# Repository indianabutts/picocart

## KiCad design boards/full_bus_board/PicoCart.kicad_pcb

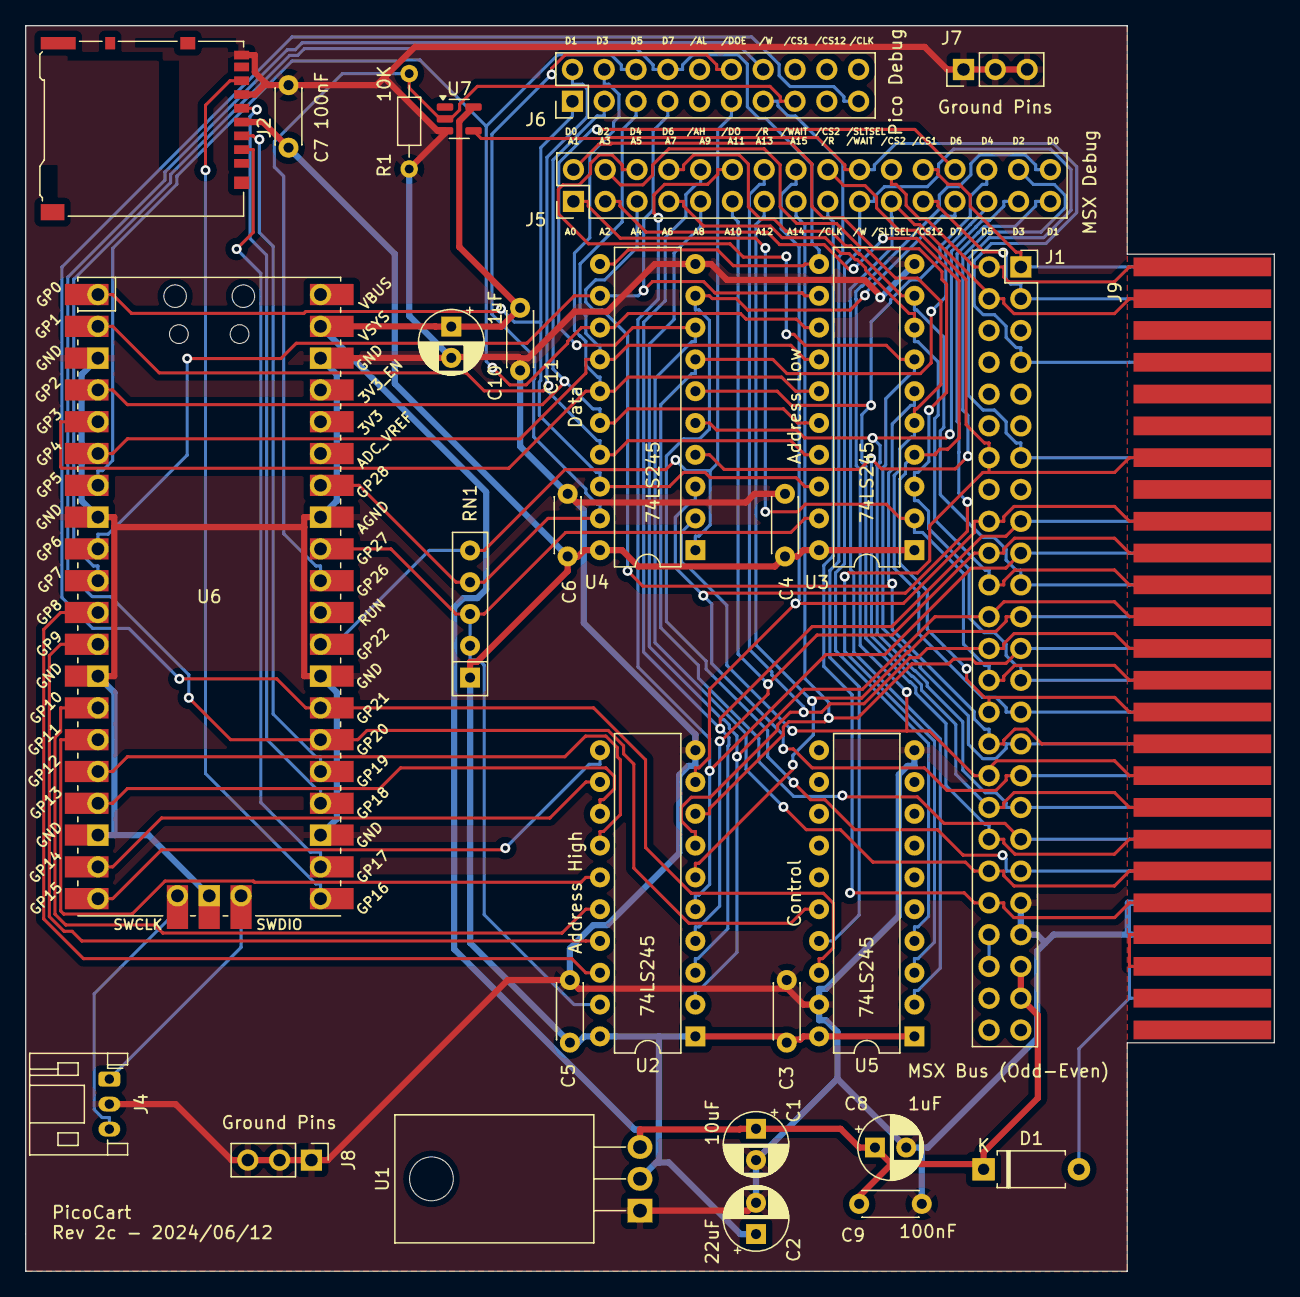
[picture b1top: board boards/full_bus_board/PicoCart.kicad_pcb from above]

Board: 2 copper layers, 99.8 x 99.5 mm, 29 parts (0 on the bottom side), 67 nets.

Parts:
C1: 10uF; CP_Radial_D5.0mm_P2.50mm
C2: 22uF; CP_Radial_D5.0mm_P2.50mm
C3, C4, C5, C6, C7, C9, C11: 100nF; C_Disc_D4.3mm_W1.9mm_P5.00mm
C8, C10: 1uF; CP_Radial_D5.0mm_P2.50mm
D1: D; D_A-405_P7.62mm_Horizontal
J1: MSX Bus (Odd-Even); PinHeader_2x25_P2.54mm_Vertical
J2: Micro_SD_Card; microSD_HC_Hirose_DM3AT-SF-PEJM5
J4: DEBUG; JST_PH_S3B-PH-K_1x03_P2.00mm_Horizontal
J5: MSX Debug; PinHeader_2x16_P2.54mm_Vertical
J6: Pico Debug; PinHeader_2x10_P2.54mm_Vertical
J7, J8: Ground Pins; PinHeader_1x03_P2.54mm_Vertical
J9: Edge Connector; MSX_Cartridge
R1: 10K; R_Axial_DIN0204_L3.6mm_D1.6mm_P7.62mm_Horizontal
RN1: 10K; R_Array_SIP5
U1: LD1117S33TR_SOT223; TO-220-3_Horizontal_TabDown
U2, U3, U4, U5: 74LS245; DIP-20_W7.62mm
U6: Pico; RPi_Pico_SMD_TH
U7: SN74LV1T34DBV; SOT-23-5

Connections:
+3.3V: C2.1, C3.1, C4.1, C5.1, C6.1, C7.1, J2.4 (VDD), RN1.1 (R1.1), U1.2 (VO), U2.1 (A->B), U2.20 (VCC), U3.1 (A->B), U3.20 (VCC), U4.20 (VCC), U5.1 (A->B), U5.20 (VCC)
+5V: C1.1, C8.1, C9.1, C10.1, C11.1, D1.1 (K), J1.45, J1.47, U1.3 (VI), U6.39 (VSYS), U7.5 (VCC)
/E_A0: J1.28, J5.1, J9.28, U3.2 (A0)
/E_A1: J1.27, J5.2, J9.27, U3.3 (A1)
/E_A2: J1.30, J5.3, J9.30, U3.4 (A2)
/E_A3: J1.29, J5.4, J9.29, U3.5 (A3)
/E_A4: J1.32, J5.5, J9.32, U3.6 (A4)
/E_A5: J1.31, J5.6, J9.31, U3.7 (A5)
/E_A6: J1.22, J5.7, J9.22, U3.8 (A6)
/E_A7: J1.21, J5.8, J9.21, U3.9 (A7)
/E_A8: J1.24, J5.9, J9.24, U2.2 (A0)
/E_A9: J1.17, J5.10, J9.17, U2.3 (A1)
/E_A10: J1.20, J5.11, J9.20, U2.4 (A2)
/E_A11: J1.19, J5.12, J9.19, U2.5 (A3)
/E_A12: J1.23, J5.13, J9.23, U2.6 (A4)
/E_A13: J1.26, J5.14, J9.26, U2.7 (A5)
/E_A14: J1.25, J5.15, J9.25, U2.8 (A6)
/E_A15: J1.18, J5.16, J9.18, U2.9 (A7)
/E_D0: J1.34, J5.32, J9.34, U4.2 (A0)
/E_D1: J1.33, J5.31, J9.33, U4.3 (A1)
/E_D2: J1.36, J5.30, J9.36, U4.4 (A2)
/E_D3: J1.35, J5.29, J9.35, U4.5 (A3)
/E_D4: J1.38, J5.28, J9.38, U4.6 (A4)
/E_D5: J1.37, J5.27, J9.37, U4.7 (A5)
/E_D6: J1.40, J5.26, J9.40, U4.8 (A6)
/E_D7: J1.39, J5.25, J9.39, U4.9 (A7)
/I_D0: J6.1, U3.18 (B0), U4.18 (B0), U6.1 (GPIO0)
/I_D1: J6.2, U3.17 (B1), U4.17 (B1), U6.2 (GPIO1)
/I_D2: J6.3, U3.16 (B2), U4.16 (B2), U6.4 (GPIO2)
/I_D3: J6.4, U3.15 (B3), U4.15 (B3), U6.5 (GPIO3)
/I_D4: J6.5, U3.14 (B4), U4.14 (B4), U6.6 (GPIO4)
/I_D5: J6.6, U3.13 (B5), U4.13 (B5), U6.7 (GPIO5)
/I_D6: J6.7, U3.12 (B6), U4.12 (B6), U6.9 (GPIO6)
/I_D7: J6.8, U3.11 (B7), U4.11 (B7), U6.10 (GPIO7)
/I_D8: U2.18 (B0), U6.11 (GPIO8)
/I_D9: U2.17 (B1), U6.12 (GPIO9)
/I_D10: U2.16 (B2), U6.14 (GPIO10)
/I_D11: U2.15 (B3), U6.15 (GPIO11)
/I_D12: U2.14 (B4), U6.16 (GPIO12)
/I_D13: U2.13 (B5), U6.17 (GPIO13)
/I_D14: U2.12 (B6), U6.19 (GPIO14)
/I_D15: U2.11 (B7), U6.20 (GPIO15)
E_CLK: J1.42, J5.17, J9.42
GND: C1.2, C2.2, C3.2, C4.2, C5.2, C6.2, C7.2, C8.2, C9.2, C10.2, C11.2, J1.41, J1.43, J2.6 (VSS), J2.9 (SHIELD), J4.2, J7.1, J7.2, J7.3, J8.1, J8.2, J8.3, J9.41, J9.43, R1.1, U1.1 (GND), U2.10 (GND), U3.10 (GND), U4.10 (GND), U5.10 (GND), U5.19 (CE), U6.3 (GND), U6.8 (GND), U6.13 (GND), U6.18 (GND), U6.23 (GND), U6.28 (GND), U6.33 (AGND), U6.38 (GND), U6.42 (GND), U7.3 (GND)
unnamed: D1.2 (A), J9.45, J9.47
unnamed: J1.44, J1.46
unnamed: J4.1, U6.43 (SWDIO)
unnamed: J4.3, U6.41 (SWCLK)
unnamed: J9.44, J9.46
SPI_CS: J2.2 (DAT3/CD), U6.22 (GPIO17)
SPI_MISO: J2.7 (DAT0), U6.21 (GPIO16)
SPI_MOSI: J2.3 (CMD), U6.25 (GPIO19)
SPI_SCK: J2.5 (CLK), U6.24 (GPIO18)
/AOE: RN1.2 (R1.2), RN1.3 (R2.2), U2.19 (CE), U3.19 (CE), U6.32 (GPIO27_ADC1)
/DOE: J6.12, RN1.4 (R3.2), U4.19 (CE), U6.34 (GPIO28_ADC2)
/DOUT: J6.11, RN1.5 (R4.2), U4.1 (A->B), U6.29 (GPIO22)
/E_CS1: J1.1, J5.24, J9.1
/E_CS2: J1.2, J5.22, J9.2
/E_CS12: J1.3, J5.23, J9.3
/E_READ: J1.14, J5.18, J9.14, U5.3 (A1)
/E_SLTSEL: J1.4, J5.21, J9.4, U5.2 (A0)
/E_WRITE: J1.13, J5.19, J9.13, U5.4 (A2)
/I_READ: J6.13, U5.17 (B1)
/I_SLTSEL: J6.19, U5.18 (B0), U6.27 (GPIO21)
/I_WAIT: J6.15, R1.2, U6.31 (GPIO26_ADC0), U7.2 (A)
/I_WRITE: J6.14, U5.16 (B2), U6.26 (GPIO20)
/WAIT: J1.7, J5.20, J9.7, U7.4 (Y)

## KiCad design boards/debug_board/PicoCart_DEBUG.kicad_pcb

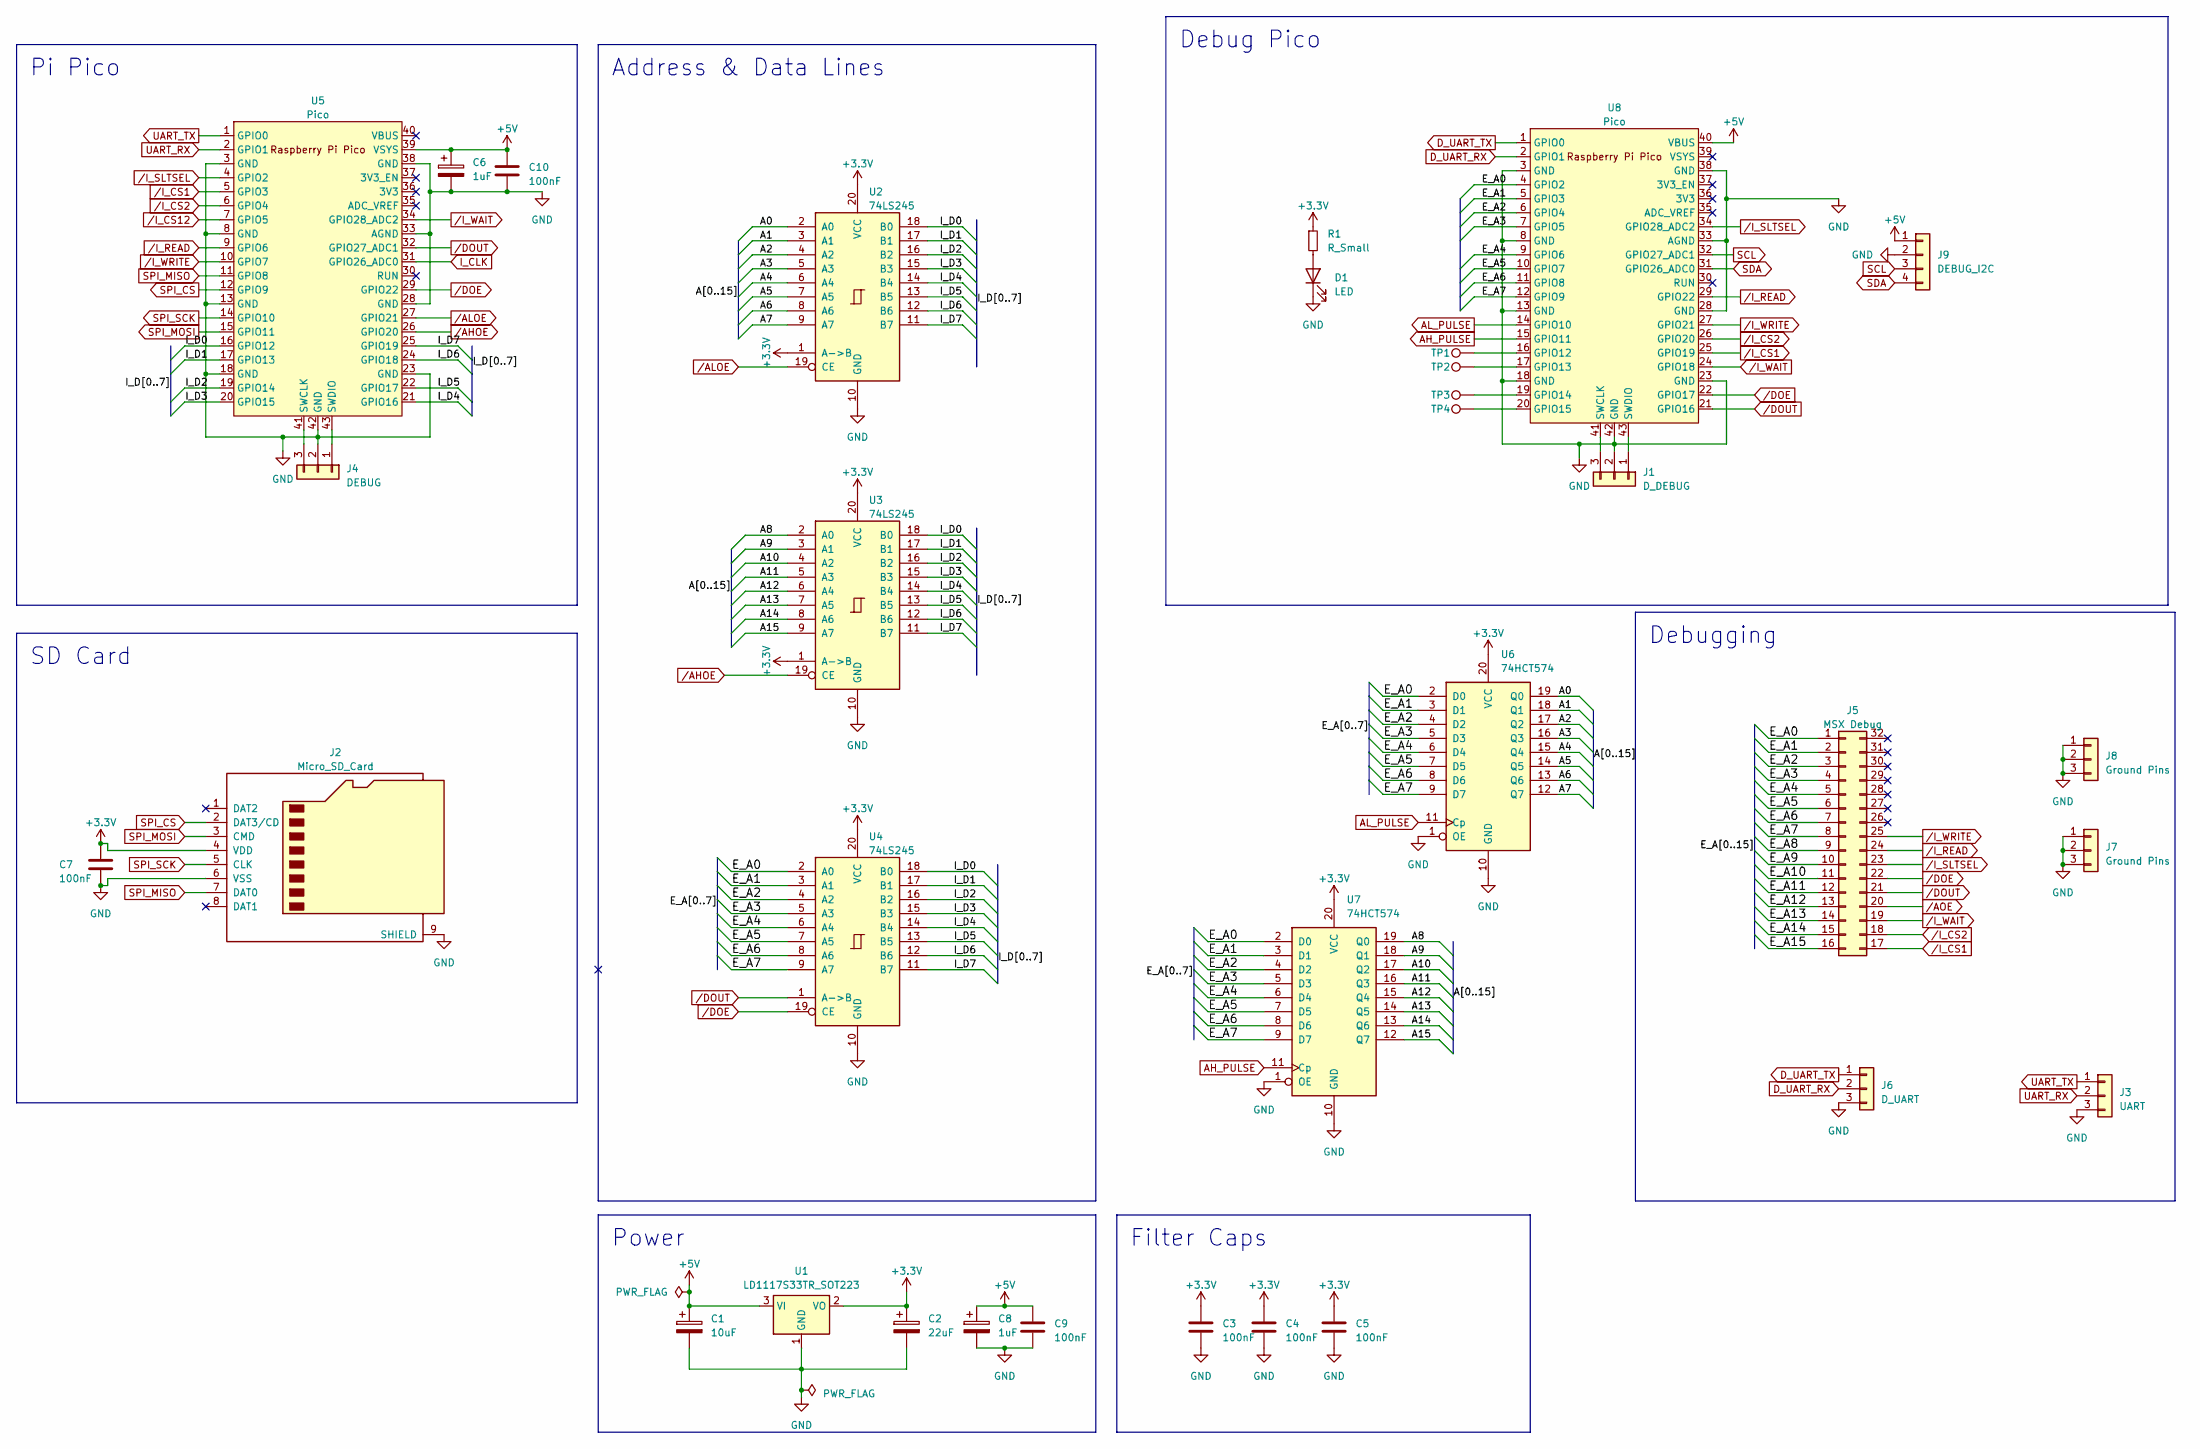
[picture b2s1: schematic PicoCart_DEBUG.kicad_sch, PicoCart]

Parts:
C1: 10uF; CP_Radial_D5.0mm_P2.50mm
C2: 22uF; CP_Radial_D5.0mm_P2.50mm
C3, C4, C5, C7, C9, C10: 100nF; C_Disc_D4.3mm_W1.9mm_P5.00mm
C6, C8: 1uF; CP_Radial_D5.0mm_P2.50mm
D1: LED; LED_D5.0mm
J1: D_DEBUG; PinSocket_1x03_P2.54mm_Vertical
J2: Micro_SD_Card; microSD_HC_Hirose_DM3AT-SF-PEJM5
J3: UART; PinSocket_1x03_P2.54mm_Vertical
J4: DEBUG; PinSocket_1x03_P2.54mm_Vertical
J5: MSX Debug; PinHeader_2x16_P2.54mm_Vertical
J6: D_UART; PinSocket_1x03_P2.54mm_Vertical
J7, J8: Ground Pins; PinHeader_1x03_P2.54mm_Vertical
J9: DEBUG_I2C; PinHeader_1x04_P2.54mm_Vertical
R1: R_Small; R_Axial_DIN0207_L6.3mm_D2.5mm_P15.24mm_Horizontal
TP1, TP2, TP3, TP4: TestPoint; TestPoint_Pad_D1.0mm
U1: LD1117S33TR_SOT223; TO-220-3_Horizontal_TabDown
U2, U3, U4: 74LS245; DIP-20_W7.62mm
U5, U8: Pico; RPi_Pico_SMD_TH
U6, U7: 74HCT574; DIP-20_W7.62mm_Socket_LongPads

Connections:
+3.3V: C2.1, C3.1, C4.1, C5.1, C7.1, J2.4 (VDD), R1.1, U1.2 (VO), U2.1 (A->B), U2.20 (VCC), U3.1 (A->B), U3.20 (VCC), U4.20 (VCC), U6.20 (VCC), U7.20 (VCC)
+5V: C1.1, C6.1, C8.1, C9.1, C10.1, J9.1, U1.3 (VI), U5.39 (VSYS), U8.40 (VBUS)
/A0: U2.2 (A0), U6.19 (Q0)
/A1: U2.3 (A1), U6.18 (Q1)
/A2: U2.4 (A2), U6.17 (Q2)
/A3: U2.5 (A3), U6.16 (Q3)
/A4: U2.6 (A4), U6.15 (Q4)
/A5: U2.7 (A5), U6.14 (Q5)
/A6: U2.8 (A6), U6.13 (Q6)
/A7: U2.9 (A7), U6.12 (Q7)
/A8: U3.2 (A0), U7.19 (Q0)
/A9: U3.3 (A1), U7.18 (Q1)
/A10: U3.4 (A2), U7.17 (Q2)
/A11: U3.5 (A3), U7.16 (Q3)
/A12: U3.6 (A4), U7.15 (Q4)
/A13: U3.7 (A5), U7.14 (Q5)
/A14: U3.8 (A6), U7.13 (Q6)
/A15: U3.9 (A7), U7.12 (Q7)
/E_A0: J5.1, U4.2 (A0), U6.2 (D0), U7.2 (D0), U8.4 (GPIO2)
/E_A1: J5.2, U4.3 (A1), U6.3 (D1), U7.3 (D1), U8.5 (GPIO3)
/E_A2: J5.3, U4.4 (A2), U6.4 (D2), U7.4 (D2), U8.6 (GPIO4)
/E_A3: J5.4, U4.5 (A3), U6.5 (D3), U7.5 (D3), U8.7 (GPIO5)
/E_A4: J5.5, U4.6 (A4), U6.6 (D4), U7.6 (D4), U8.9 (GPIO6)
/E_A5: J5.6, U4.7 (A5), U6.7 (D5), U7.7 (D5), U8.10 (GPIO7)
/E_A6: J5.7, U4.8 (A6), U6.8 (D6), U7.8 (D6), U8.11 (GPIO8)
/E_A7: J5.8, U4.9 (A7), U6.9 (D7), U7.9 (D7), U8.12 (GPIO9)
/E_A8: J5.9
/E_A9: J5.10
/E_A10: J5.11
/E_A11: J5.12
/E_A12: J5.13
/E_A13: J5.14
/E_A14: J5.15
/E_A15: J5.16
/I_D0: U2.18 (B0), U3.18 (B0), U4.18 (B0), U5.16 (GPIO12)
/I_D1: U2.17 (B1), U3.17 (B1), U4.17 (B1), U5.17 (GPIO13)
/I_D2: U2.16 (B2), U3.16 (B2), U4.16 (B2), U5.19 (GPIO14)
/I_D3: U2.15 (B3), U3.15 (B3), U4.15 (B3), U5.20 (GPIO15)
/I_D4: U2.14 (B4), U3.14 (B4), U4.14 (B4), U5.21 (GPIO16)
/I_D5: U2.13 (B5), U3.13 (B5), U4.13 (B5), U5.22 (GPIO17)
/I_D6: U2.12 (B6), U3.12 (B6), U4.12 (B6), U5.24 (GPIO18)
/I_D7: U2.11 (B7), U3.11 (B7), U4.11 (B7), U5.25 (GPIO19)
AH_PULSE: U7.11 (Cp), U8.15 (GPIO11)
AL_PULSE: U6.11 (Cp), U8.14 (GPIO10)
D_UART_RX: J6.2, U8.2 (GPIO1)
D_UART_TX: J6.1, U8.1 (GPIO0)
GND: C1.2, C2.2, C3.2, C4.2, C5.2, C6.2, C7.2, C8.2, C9.2, C10.2, D1.1 (K), J1.2, J2.6 (VSS), J2.9 (SHIELD), J3.3, J4.2, J6.3, J7.1, J7.2, J7.3, J8.1, J8.2, J8.3, J9.2, U1.1 (GND), U2.10 (GND), U3.10 (GND), U4.10 (GND), U5.3 (GND), U5.8 (GND), U5.13 (GND), U5.18 (GND), U5.23 (GND), U5.28 (GND), U5.33 (AGND), U5.38 (GND), U5.42 (GND), U6.1 (OE), U6.10 (GND), U7.1 (OE), U7.10 (GND), U8.3 (GND), U8.8 (GND), U8.13 (GND), U8.18 (GND), U8.23 (GND), U8.28 (GND), U8.33 (AGND), U8.38 (GND), U8.42 (GND)
I_CLK: U5.31 (GPIO26_ADC0)
unnamed: D1.2 (A), R1.2
unnamed: J1.1, U8.43 (SWDIO)
unnamed: J1.3, U8.41 (SWCLK)
unnamed: J4.1, U5.43 (SWDIO)
unnamed: J4.3, U5.41 (SWCLK)
unnamed: TP1.1, U8.16 (GPIO12)
unnamed: TP2.1, U8.17 (GPIO13)
unnamed: TP3.1, U8.19 (GPIO14)
unnamed: TP4.1, U8.20 (GPIO15)
SCL: J9.3, U8.32 (GPIO27_ADC1)
SDA: J9.4, U8.31 (GPIO26_ADC0)
SPI_CS: J2.2 (DAT3/CD), U5.12 (GPIO9)
SPI_MISO: J2.7 (DAT0), U5.11 (GPIO8)
SPI_MOSI: J2.3 (CMD), U5.15 (GPIO11)
SPI_SCK: J2.5 (CLK), U5.14 (GPIO10)
UART_RX: J3.2, U5.2 (GPIO1)
UART_TX: J3.1, U5.1 (GPIO0)
/AHOE: U3.19 (CE), U5.26 (GPIO20)
/ALOE: U2.19 (CE), U5.27 (GPIO21)
/AOE: J5.20
/DOE: J5.22, U4.19 (CE), U5.29 (GPIO22), U8.22 (GPIO17)
/DOUT: J5.21, U4.1 (A->B), U5.32 (GPIO27_ADC1), U8.21 (GPIO16)
/I_CS1: J5.17, U5.5 (GPIO3), U8.25 (GPIO19)
/I_CS2: J5.18, U5.6 (GPIO4), U8.26 (GPIO20)
/I_CS12: U5.7 (GPIO5)
/I_READ: J5.24, U5.9 (GPIO6), U8.29 (GPIO22)
/I_SLTSEL: J5.23, U5.4 (GPIO2), U8.34 (GPIO28_ADC2)
/I_WAIT: J5.19, U5.34 (GPIO28_ADC2), U8.24 (GPIO18)
/I_WRITE: J5.25, U5.10 (GPIO7), U8.27 (GPIO21)

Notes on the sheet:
Pi Pico
Debug Pico
Debugging
Filter Caps
Power
SD Card
Address & Data Lines

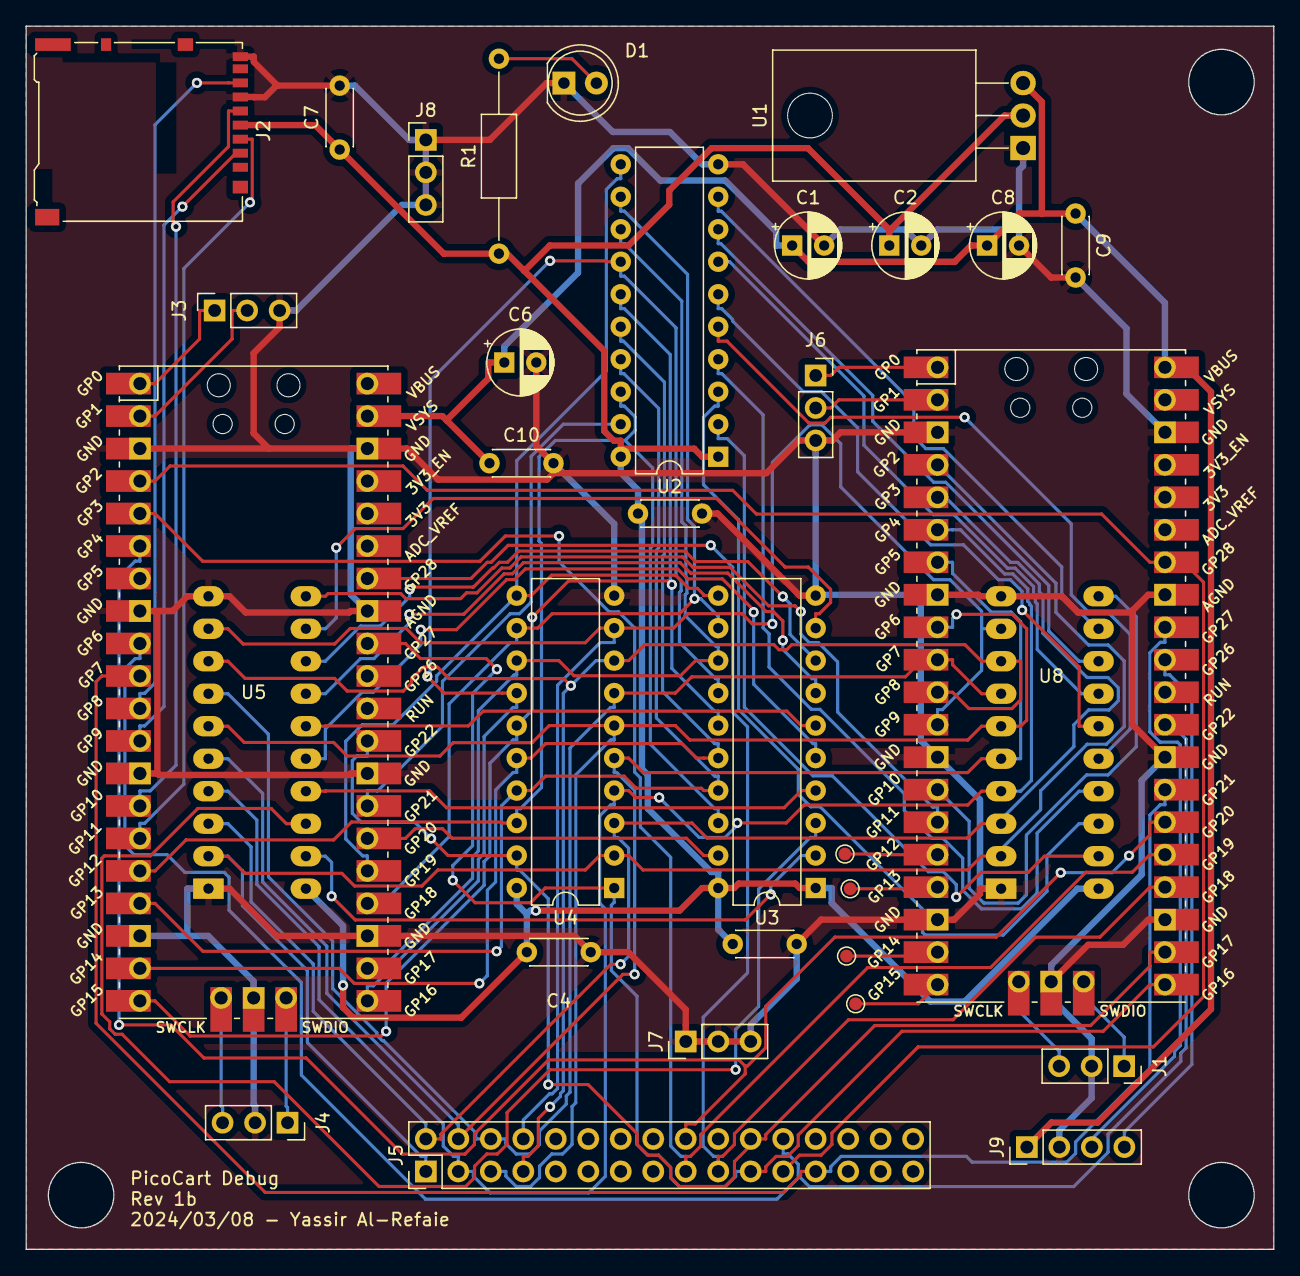
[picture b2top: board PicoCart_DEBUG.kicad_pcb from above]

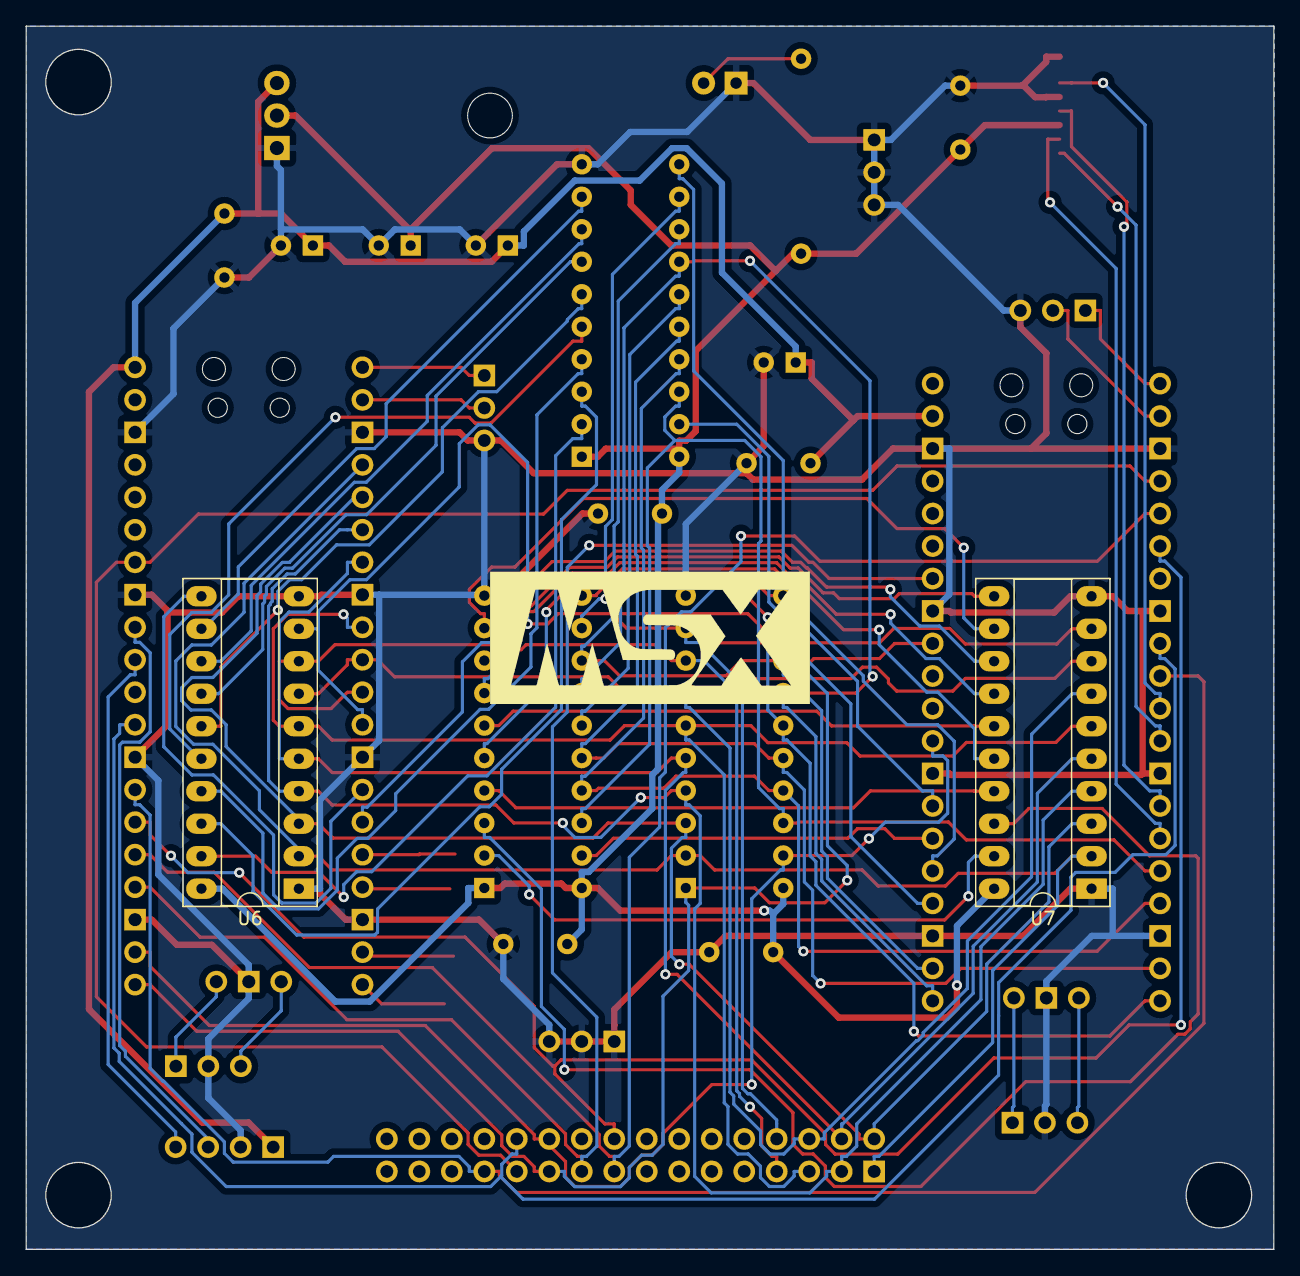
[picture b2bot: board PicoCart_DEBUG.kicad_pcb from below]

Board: 2 copper layers, 97.5 x 95.6 mm, 33 parts (2 on the bottom side), 66 nets.

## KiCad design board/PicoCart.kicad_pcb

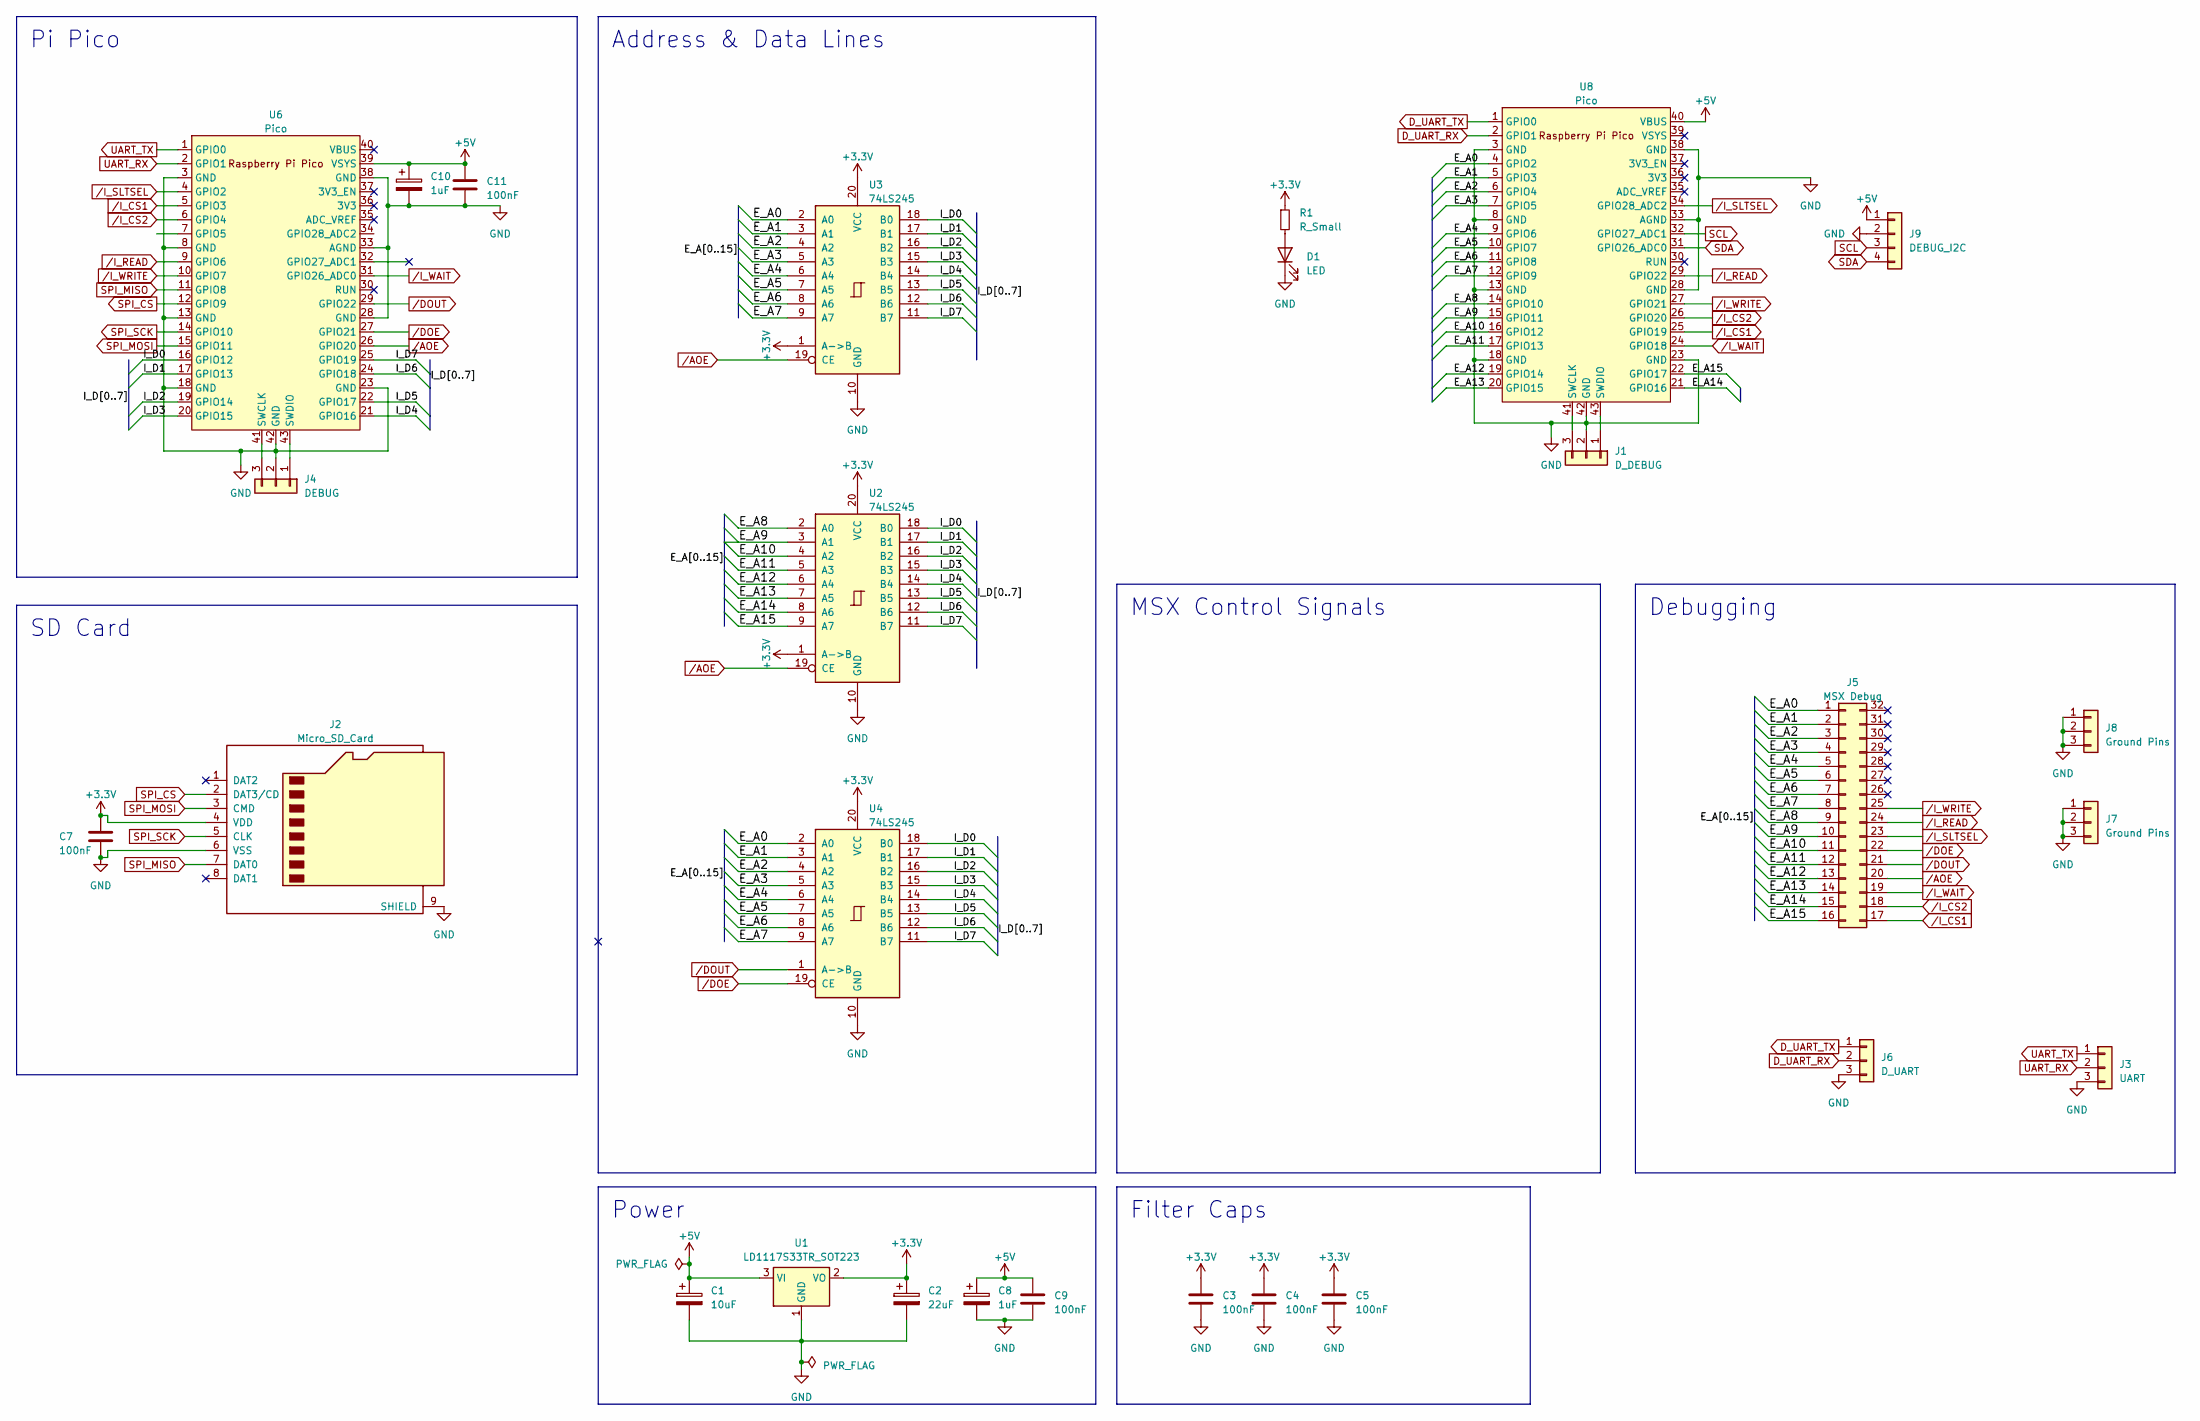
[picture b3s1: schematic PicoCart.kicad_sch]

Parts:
C1: 10uF; CP_Radial_D5.0mm_P2.50mm
C2: 22uF; CP_Radial_D5.0mm_P2.50mm
C3, C4, C5, C7, C9, C11: 100nF; C_Disc_D4.3mm_W1.9mm_P5.00mm
C8, C10: 1uF; CP_Radial_D5.0mm_P2.50mm
D1: LED; LED_D5.0mm
J1: D_DEBUG; PinSocket_1x03_P2.54mm_Vertical
J2: Micro_SD_Card; microSD_HC_Hirose_DM3AT-SF-PEJM5
J3: UART; PinSocket_1x03_P2.54mm_Vertical
J4: DEBUG; PinSocket_1x03_P2.54mm_Vertical
J5: MSX Debug; PinHeader_2x16_P2.54mm_Vertical
J6: D_UART; PinSocket_1x03_P2.54mm_Vertical
J7, J8: Ground Pins; PinHeader_1x03_P2.54mm_Vertical
J9: DEBUG_I2C; PinHeader_1x04_P2.54mm_Vertical
R1: R_Small; R_Axial_DIN0207_L6.3mm_D2.5mm_P15.24mm_Horizontal
U1: LD1117S33TR_SOT223; TO-220-3_Horizontal_TabDown
U2, U3, U4: 74LS245; DIP-20_W7.62mm
U6, U8: Pico; RPi_Pico_SMD_TH

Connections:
+3.3V: C2.1, C3.1, C4.1, C5.1, C7.1, J2.4 (VDD), R1.1, U1.2 (VO), U2.1 (A->B), U2.20 (VCC), U3.1 (A->B), U3.20 (VCC), U4.20 (VCC)
+5V: C1.1, C8.1, C9.1, C10.1, C11.1, J9.1, U1.3 (VI), U6.39 (VSYS), U8.40 (VBUS)
/E_A0: J5.1, U3.2 (A0), U4.2 (A0), U8.4 (GPIO2)
/E_A1: J5.2, U3.3 (A1), U4.3 (A1), U8.5 (GPIO3)
/E_A2: J5.3, U3.4 (A2), U4.4 (A2), U8.6 (GPIO4)
/E_A3: J5.4, U3.5 (A3), U4.5 (A3), U8.7 (GPIO5)
/E_A4: J5.5, U3.6 (A4), U4.6 (A4), U8.9 (GPIO6)
/E_A5: J5.6, U3.7 (A5), U4.7 (A5), U8.10 (GPIO7)
/E_A6: J5.7, U3.8 (A6), U4.8 (A6), U8.11 (GPIO8)
/E_A7: J5.8, U3.9 (A7), U4.9 (A7), U8.12 (GPIO9)
/E_A8: J5.9, U2.2 (A0), U8.14 (GPIO10)
/E_A9: J5.10, U2.3 (A1), U8.15 (GPIO11)
/E_A10: J5.11, U2.4 (A2), U8.16 (GPIO12)
/E_A11: J5.12, U2.5 (A3), U8.17 (GPIO13)
/E_A12: J5.13, U2.6 (A4), U8.19 (GPIO14)
/E_A13: J5.14, U2.7 (A5), U8.20 (GPIO15)
/E_A14: J5.15, U2.8 (A6), U8.21 (GPIO16)
/E_A15: J5.16, U2.9 (A7), U8.22 (GPIO17)
/I_D0: U2.18 (B0), U3.18 (B0), U4.18 (B0), U6.16 (GPIO12)
/I_D1: U2.17 (B1), U3.17 (B1), U4.17 (B1), U6.17 (GPIO13)
/I_D2: U2.16 (B2), U3.16 (B2), U4.16 (B2), U6.19 (GPIO14)
/I_D3: U2.15 (B3), U3.15 (B3), U4.15 (B3), U6.20 (GPIO15)
/I_D4: U2.14 (B4), U3.14 (B4), U4.14 (B4), U6.21 (GPIO16)
/I_D5: U2.13 (B5), U3.13 (B5), U4.13 (B5), U6.22 (GPIO17)
/I_D6: U2.12 (B6), U3.12 (B6), U4.12 (B6), U6.24 (GPIO18)
/I_D7: U2.11 (B7), U3.11 (B7), U4.11 (B7), U6.25 (GPIO19)
D_UART_RX: J6.2, U8.2 (GPIO1)
D_UART_TX: J6.1, U8.1 (GPIO0)
GND: C1.2, C2.2, C3.2, C4.2, C5.2, C7.2, C8.2, C9.2, C10.2, C11.2, D1.1 (K), J1.2, J2.6 (VSS), J2.9 (SHIELD), J3.3, J4.2, J6.3, J7.1, J7.2, J7.3, J8.1, J8.2, J8.3, J9.2, U1.1 (GND), U2.10 (GND), U3.10 (GND), U4.10 (GND), U6.3 (GND), U6.8 (GND), U6.13 (GND), U6.18 (GND), U6.23 (GND), U6.28 (GND), U6.33 (AGND), U6.38 (GND), U6.42 (GND), U8.3 (GND), U8.8 (GND), U8.13 (GND), U8.18 (GND), U8.23 (GND), U8.28 (GND), U8.33 (AGND), U8.38 (GND), U8.42 (GND)
unnamed: D1.2 (A), R1.2
unnamed: J1.1, U8.43 (SWDIO)
unnamed: J1.3, U8.41 (SWCLK)
unnamed: J4.1, U6.43 (SWDIO)
unnamed: J4.3, U6.41 (SWCLK)
SCL: J9.3, U8.32 (GPIO27_ADC1)
SDA: J9.4, U8.31 (GPIO26_ADC0)
SPI_CS: J2.2 (DAT3/CD), U6.12 (GPIO9)
SPI_MISO: J2.7 (DAT0), U6.11 (GPIO8)
SPI_MOSI: J2.3 (CMD), U6.15 (GPIO11)
SPI_SCK: J2.5 (CLK), U6.14 (GPIO10)
UART_RX: J3.2, U6.2 (GPIO1)
UART_TX: J3.1, U6.1 (GPIO0)
/AOE: J5.20, U2.19 (CE), U3.19 (CE), U6.26 (GPIO20)
/DOE: J5.22, U4.19 (CE), U6.27 (GPIO21)
/DOUT: J5.21, U4.1 (A->B), U6.29 (GPIO22)
/I_CS1: J5.17, U6.5 (GPIO3), U8.25 (GPIO19)
/I_CS2: J5.18, U6.6 (GPIO4), U8.26 (GPIO20)
/I_READ: J5.24, U6.9 (GPIO6), U8.29 (GPIO22)
/I_SLTSEL: J5.23, U6.4 (GPIO2), U8.34 (GPIO28_ADC2)
/I_WAIT: J5.19, U6.31 (GPIO26_ADC0), U8.24 (GPIO18)
/I_WRITE: J5.25, U6.10 (GPIO7), U8.27 (GPIO21)

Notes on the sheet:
Pi Pico
MSX Control Signals
Debugging
Filter Caps
Power
SD Card
Address & Data Lines

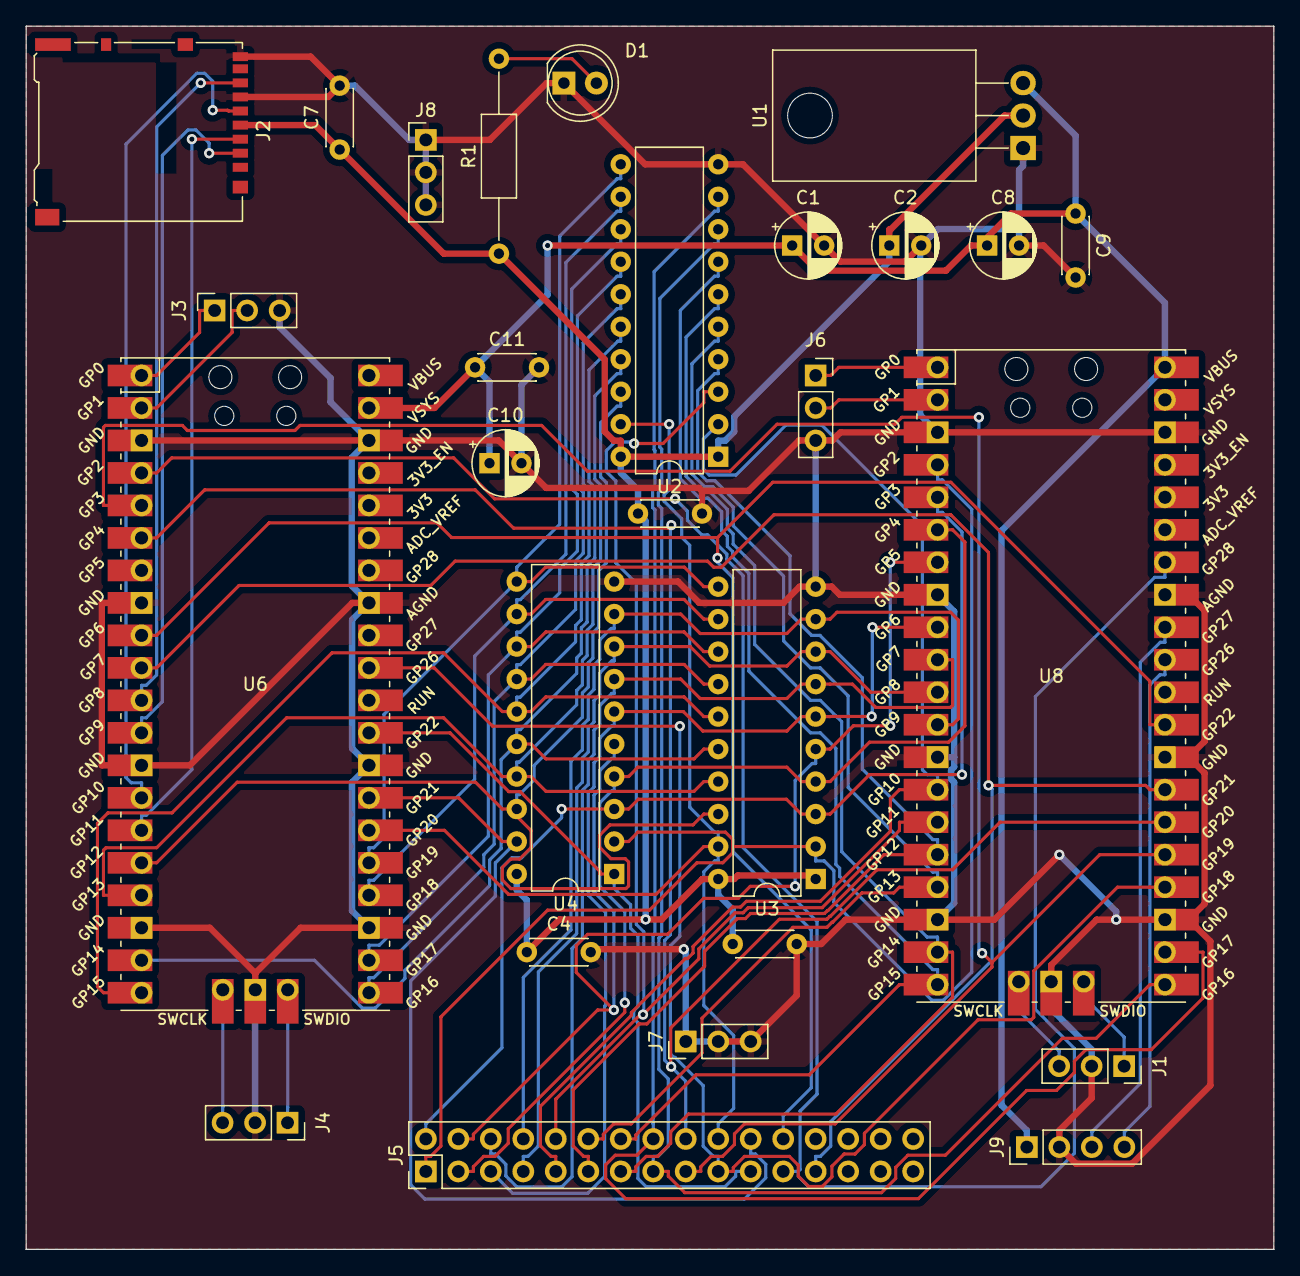
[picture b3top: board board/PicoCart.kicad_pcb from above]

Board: 2 copper layers, 97.5 x 95.6 mm, 27 parts (0 on the bottom side), 51 nets.

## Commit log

2023-04-01 DEBUG: Add src folder for python debug program
2023-04-01 DEBUG:Add Debug Logic
2023-04-01 DEBUG: Added Looped Controller
2023-04-14 moved ROM Data to separate .h file
2023-05-02 Address PIO seems to work now
2023-05-02 Removed delays in address pio
2023-08-27 Deleted everything, will start from scratch and more rigorously
2023-10-09 Add SD library for Pi Pico
2023-10-09 ignore ~ files from emacs
2023-10-09 SD Card Writes working now
2023-10-10 Now can read rom files properly
2023-10-10 Add VSCode config
2023-10-10 Reading ROM to buffer working
2023-10-10 Check cartridge header for offset and signature
2023-10-10 start control library
2023-10-10 Working on address reading, might need PIO for this
2023-10-10 start to implement address read in PIO
2023-10-11 Add compatiblity for using windows to build and debug
2023-10-11 Address read is operating, but too slow
    Working on PIO implementation of the address read logic
2024-02-17 brought board and rp2040 src together
2024-02-18 Tidied up Schematic
2024-02-18 Swapped DoE and IWait
2024-03-03 Debug Board Design
    Created a Debug board so that I can test the Main Pico logic against a
    more controllable set of signals, rather than the MSX which provides a
    very short window of usability
2024-03-03 Separate Debug and Main Board Projects
2024-03-08 Fixed circuit - last design would not have worked
2024-03-08 Add Test Points for Spare GPIO Pins
2024-03-09 restructured project to spearate debug and core
2024-03-23 Add Debug Board Src dir
2024-03-24 Added External SSD1306 Library
2024-03-24 Initial Printing to LCD Display
2024-03-24 Add fprintf_to_display function
2024-03-25 State where the display is working
2024-03-26 Display Works and Debug board triggers main board
    Not full functionality by any means, but the debug board now pulses
    nSLTSEL, which triggers an IRQ Event on the main board
    This then triggers the IRQ on the Debug board by pulsing the wait
    signal.
2024-03-27 Added Data for Debug Board
2024-03-27 Commiting current state of Core before full rewrite
2024-03-29 Started Core Logic, handshaking not working here
2024-03-31 Debug Board Read Data Confirmed working
2024-03-31 Handshaking works between the two boards now
2024-04-06 Writing Address Confirmed on Debug Board
2024-04-06 Functionally seems ok, very timing constrained
    Have all the basic functions working using GPIO and IRQs.
    It's very sensitive to the timings of everything.
    There is also an additional
2024-04-06 Working faster now, need to try with PIO now
2024-04-07 Use gpio_put_masked for data write
2024-04-07 Start PIO as a separated build target
2024-04-07 Remove FatFS Submodule
2024-04-07 Moved FatFS to source root lib folder
2024-04-07 remove unncessery commented define
2024-04-07 Restructure for PIO implementation
2024-04-07 moved libs into a shared directory to simplify structure
2024-06-12 Added 16 data lines
2024-08-09 committing code from debug board will make into 16 bit version
2024-12-11 Change GPIO Pinout for 16-bit version
2024-12-12 Started rewrite of PicoCart
    Not sure how to effectively debug this...
2024-12-13 Got it booting without interfering using individual
2024-12-13 Hand wrote the HEX for Masks and Values
2024-12-13 Seems to have an affect, which means its writing
    i think it's missing some addresses though
2024-12-17 Started PIO
